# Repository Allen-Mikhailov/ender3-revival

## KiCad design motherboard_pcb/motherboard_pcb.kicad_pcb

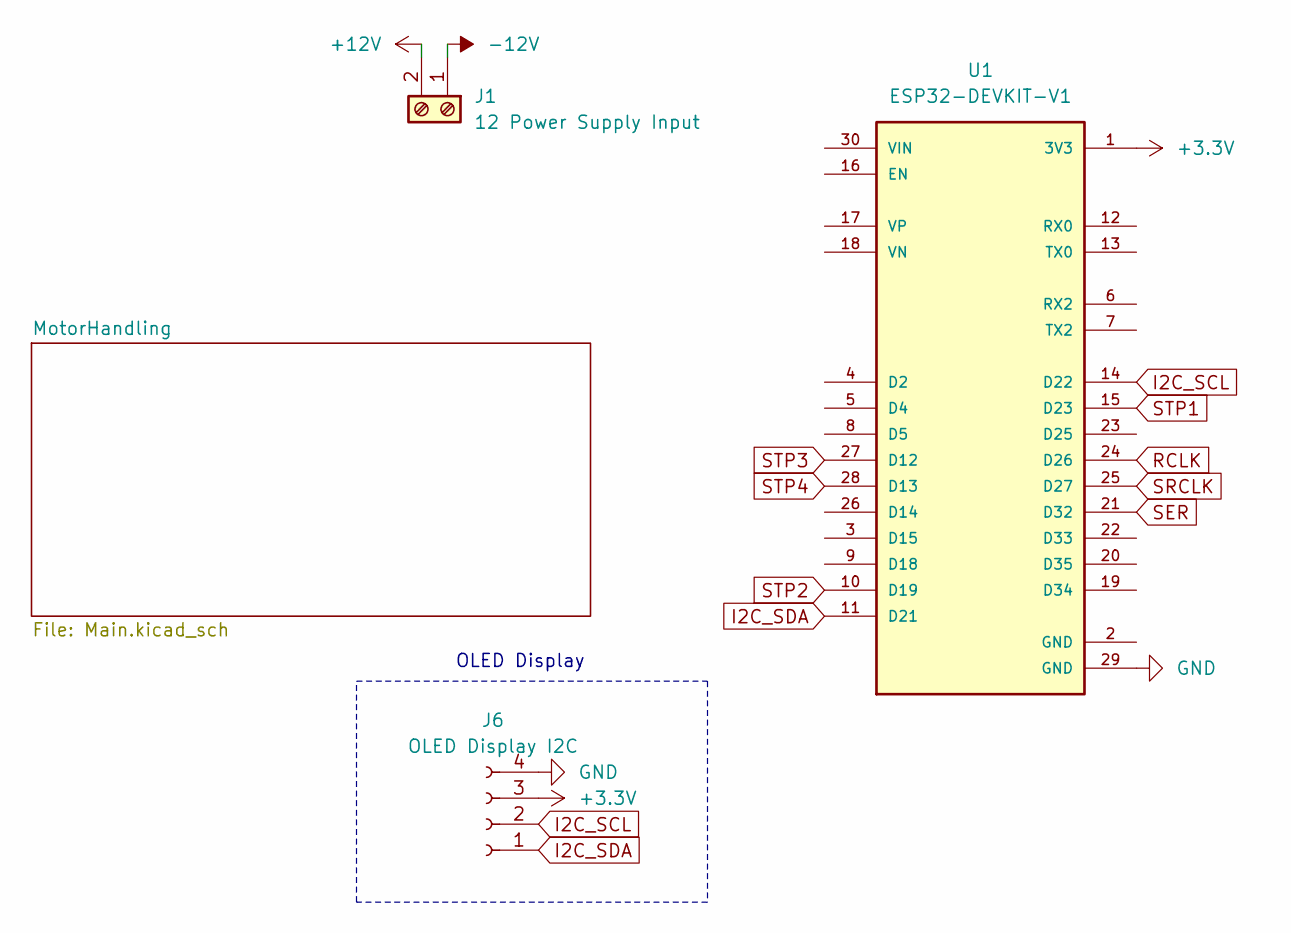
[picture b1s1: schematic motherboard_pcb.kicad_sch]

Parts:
J1: 12 Power Supply Input; TerminalBlock_Xinya_XY308-2.54-2P_1x02_P2.54mm_Horizontal
J6: OLED Display I2C; PinSocket_1x04_P2.54mm_Vertical
U1: ESP32-DEVKIT-V1; MODULE_ESP32_DEVKIT_V1; PARTREV N/A

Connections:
+3.3V: J6.3, U1.1 (3V3); also elsewhere on the board
+12V: J1.2; also elsewhere on the board
-12V: J1.1; also elsewhere on the board
GND: J6.4, U1.29 (GND); also elsewhere on the board
I2C_SCL: J6.2, U1.14 (D22)
I2C_SDA: J6.1, U1.11 (D21)
RCLK: U1.24 (D26); also elsewhere on the board
SER: U1.21 (D32); also elsewhere on the board
SRCLK: U1.25 (D27); also elsewhere on the board
STP1: U1.15 (D23); also elsewhere on the board
STP2: U1.10 (D19); also elsewhere on the board
STP3: U1.27 (D12); also elsewhere on the board
STP4: U1.28 (D13); also elsewhere on the board

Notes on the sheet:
OLED Display

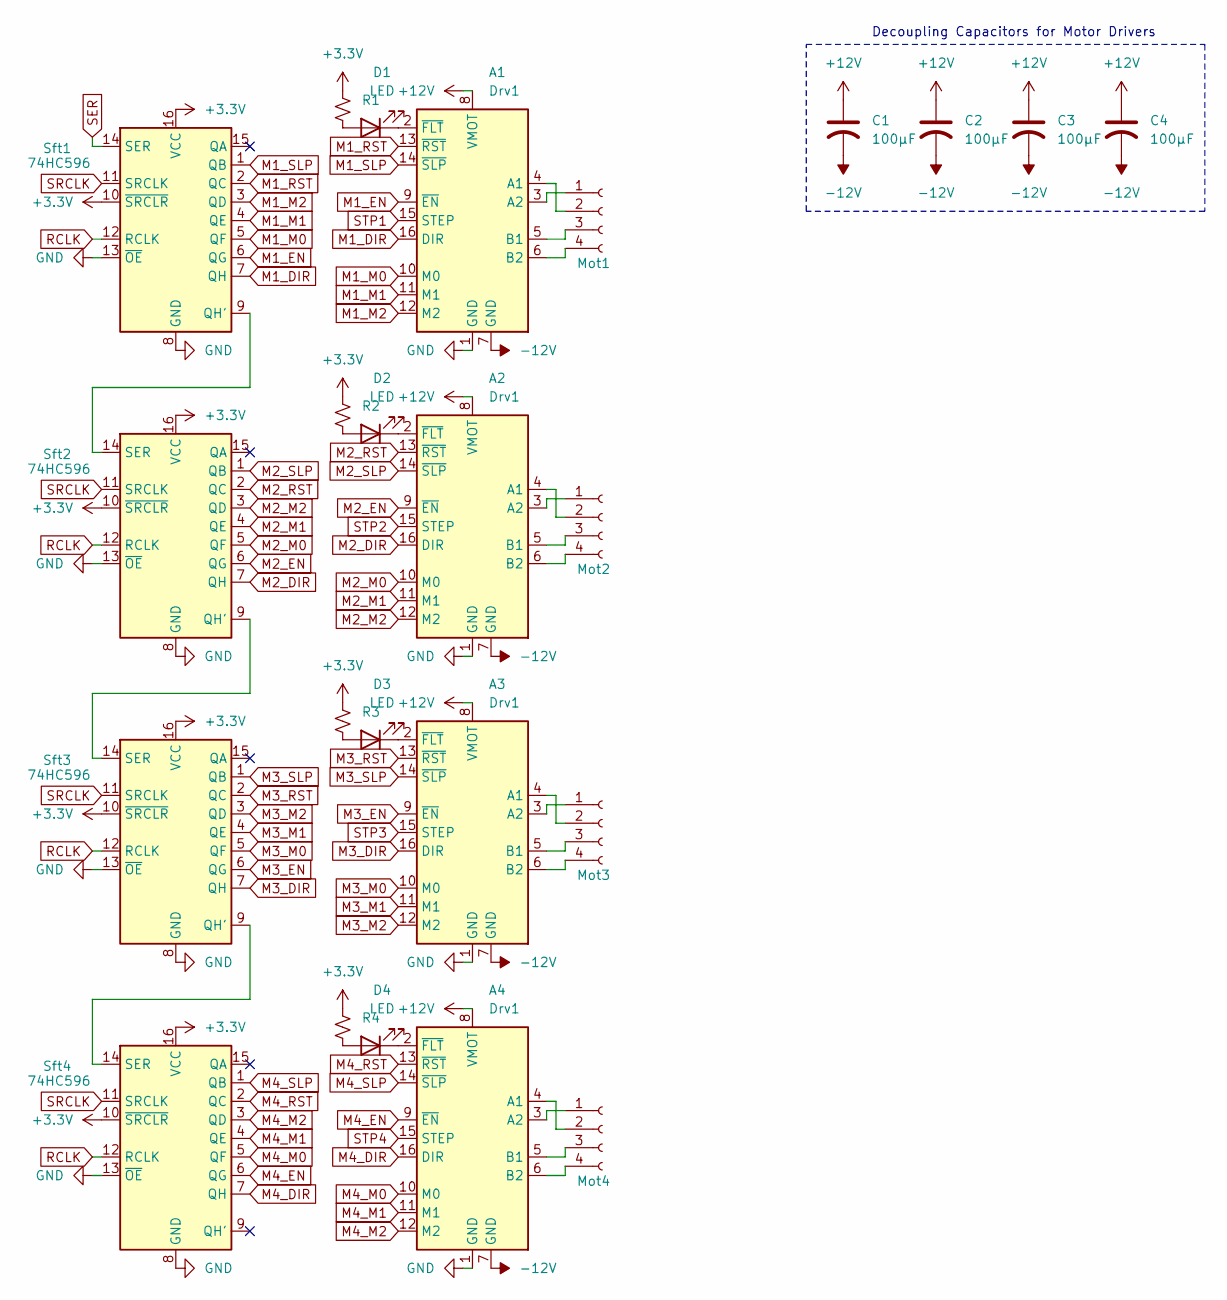
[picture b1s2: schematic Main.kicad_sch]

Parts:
A1, A2, A3, A4: Drv1; Pololu_Breakout-16_15.2x20.3mm
C1, C2, C3, C4: 100µF; CP_Radial_D5.0mm_P2.50mm
D1, D2, D3, D4: LED; LED_D3.0mm
Mot1, Mot2, Mot3, Mot4: Conn_01x04_Socket; JST_PH_B4B-PH-K_1x04_P2.00mm_Vertical
R1, R2, R3, R4: 65; R_Axial_DIN0207_L6.3mm_D2.5mm_P10.16mm_Horizontal
Sft1, Sft2, Sft3, Sft4: 74HC596; DIP-16_W7.62mm

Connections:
+3.3V: R1.1, R2.1, R3.1, R4.1, Sft1.10 (~SRCLR), Sft1.16 (VCC), Sft2.10 (~SRCLR), Sft2.16 (VCC), Sft3.10 (~SRCLR), Sft3.16 (VCC), Sft4.10 (~SRCLR), Sft4.16 (VCC); also elsewhere on the board
+12V: A1.8 (VMOT), A2.8 (VMOT), A3.8 (VMOT), A4.8 (VMOT), C1.1, C2.1, C3.1, C4.1; also elsewhere on the board
-12V: A1.7 (GND), A2.7 (GND), A3.7 (GND), A4.7 (GND), C1.2, C2.2, C3.2, C4.2; also elsewhere on the board
GND: A1.1 (GND), A2.1 (GND), A3.1 (GND), A4.1 (GND), Sft1.8 (GND), Sft1.13 (~OE), Sft2.8 (GND), Sft2.13 (~OE), Sft3.8 (GND), Sft3.13 (~OE), Sft4.8 (GND), Sft4.13 (~OE); also elsewhere on the board
M1_DIR: A1.16 (DIR), Sft1.7 (QH)
M1_EN: A1.9 (~EN), Sft1.6 (QG)
M1_M0: A1.10 (M0), Sft1.5 (QF)
M1_M1: A1.11 (M1), Sft1.4 (QE)
M1_M2: A1.12 (M2), Sft1.3 (QD)
M1_RST: A1.13 (~RST), Sft1.2 (QC)
M1_SLP: A1.14 (~SLP), Sft1.1 (QB)
M2_DIR: A2.16 (DIR), Sft2.7 (QH)
M2_EN: A2.9 (~EN), Sft2.6 (QG)
M2_M0: A2.10 (M0), Sft2.5 (QF)
M2_M1: A2.11 (M1), Sft2.4 (QE)
M2_M2: A2.12 (M2), Sft2.3 (QD)
M2_RST: A2.13 (~RST), Sft2.2 (QC)
M2_SLP: A2.14 (~SLP), Sft2.1 (QB)
M3_DIR: A3.16 (DIR), Sft3.7 (QH)
M3_EN: A3.9 (~EN), Sft3.6 (QG)
M3_M0: A3.10 (M0), Sft3.5 (QF)
M3_M1: A3.11 (M1), Sft3.4 (QE)
M3_M2: A3.12 (M2), Sft3.3 (QD)
M3_RST: A3.13 (~RST), Sft3.2 (QC)
M3_SLP: A3.14 (~SLP), Sft3.1 (QB)
M4_DIR: A4.16 (DIR), Sft4.7 (QH)
M4_EN: A4.9 (~EN), Sft4.6 (QG)
M4_M0: A4.10 (M0), Sft4.5 (QF)
M4_M1: A4.11 (M1), Sft4.4 (QE)
M4_M2: A4.12 (M2), Sft4.3 (QD)
M4_RST: A4.13 (~RST), Sft4.2 (QC)
M4_SLP: A4.14 (~SLP), Sft4.1 (QB)
unnamed: A1.4 (A1), Mot1.2
unnamed: A1.3 (A2), Mot1.1
unnamed: A1.5 (B1), Mot1.3
unnamed: A1.6 (B2), Mot1.4
unnamed: A1.2 (~FLT), D1.1 (K)
unnamed: A2.4 (A1), Mot2.2
unnamed: A2.3 (A2), Mot2.1
unnamed: A2.5 (B1), Mot2.3
unnamed: A2.6 (B2), Mot2.4
unnamed: A2.2 (~FLT), D2.1 (K)
unnamed: A3.4 (A1), Mot3.2
unnamed: A3.3 (A2), Mot3.1
unnamed: A3.5 (B1), Mot3.3
unnamed: A3.6 (B2), Mot3.4
unnamed: A3.2 (~FLT), D3.1 (K)
unnamed: A4.4 (A1), Mot4.2
unnamed: A4.3 (A2), Mot4.1
unnamed: A4.5 (B1), Mot4.3
unnamed: A4.6 (B2), Mot4.4
unnamed: A4.2 (~FLT), D4.1 (K)
unnamed: D1.2 (A), R1.2
unnamed: D2.2 (A), R2.2
unnamed: D3.2 (A), R3.2
unnamed: D4.2 (A), R4.2
unnamed: Sft1.9 (QH'), Sft2.14 (SER)
unnamed: Sft2.9 (QH'), Sft3.14 (SER)
unnamed: Sft3.9 (QH'), Sft4.14 (SER)
RCLK: Sft1.12 (RCLK), Sft2.12 (RCLK), Sft3.12 (RCLK), Sft4.12 (RCLK); also elsewhere on the board
SER: Sft1.14 (SER); also elsewhere on the board
SRCLK: Sft1.11 (SRCLK), Sft2.11 (SRCLK), Sft3.11 (SRCLK), Sft4.11 (SRCLK); also elsewhere on the board
STP1: A1.15 (STEP); also elsewhere on the board
STP2: A2.15 (STEP); also elsewhere on the board
STP3: A3.15 (STEP); also elsewhere on the board
STP4: A4.15 (STEP); also elsewhere on the board

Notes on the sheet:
Decoupling Capacitors for Motor Drivers

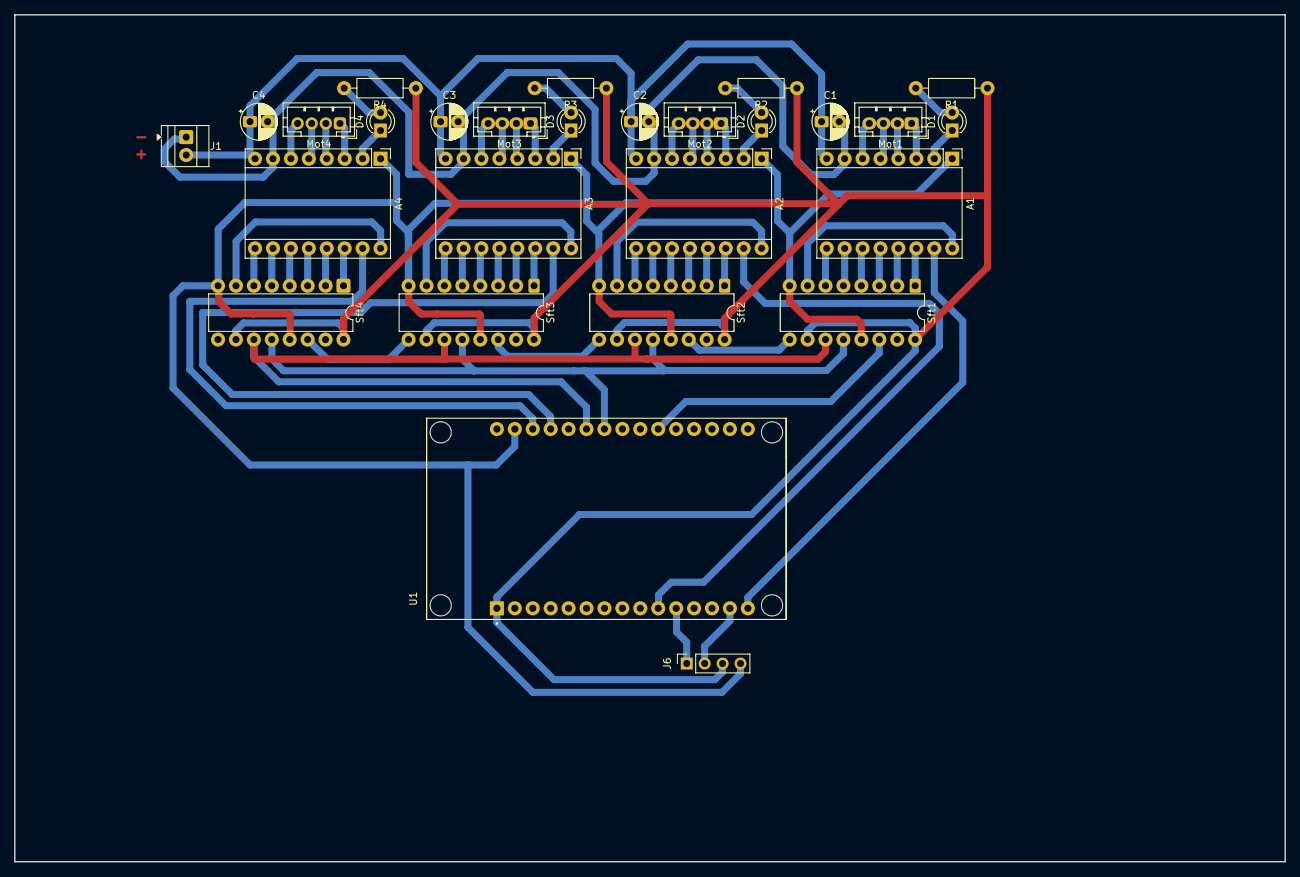
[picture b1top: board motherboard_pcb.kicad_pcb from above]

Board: 2 copper layers, 180.0 x 120.0 mm, 27 parts (0 on the bottom side), 68 nets.

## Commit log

2025-07-06 Work done on schematic of the main board
2025-07-07 Added connections for OLED display
2025-07-22 Added shift registers to the skematic and started attempting to route
2025-08-03 Most of the motor stuff has been routed
2025-08-09 Routed all connections to shift registers
